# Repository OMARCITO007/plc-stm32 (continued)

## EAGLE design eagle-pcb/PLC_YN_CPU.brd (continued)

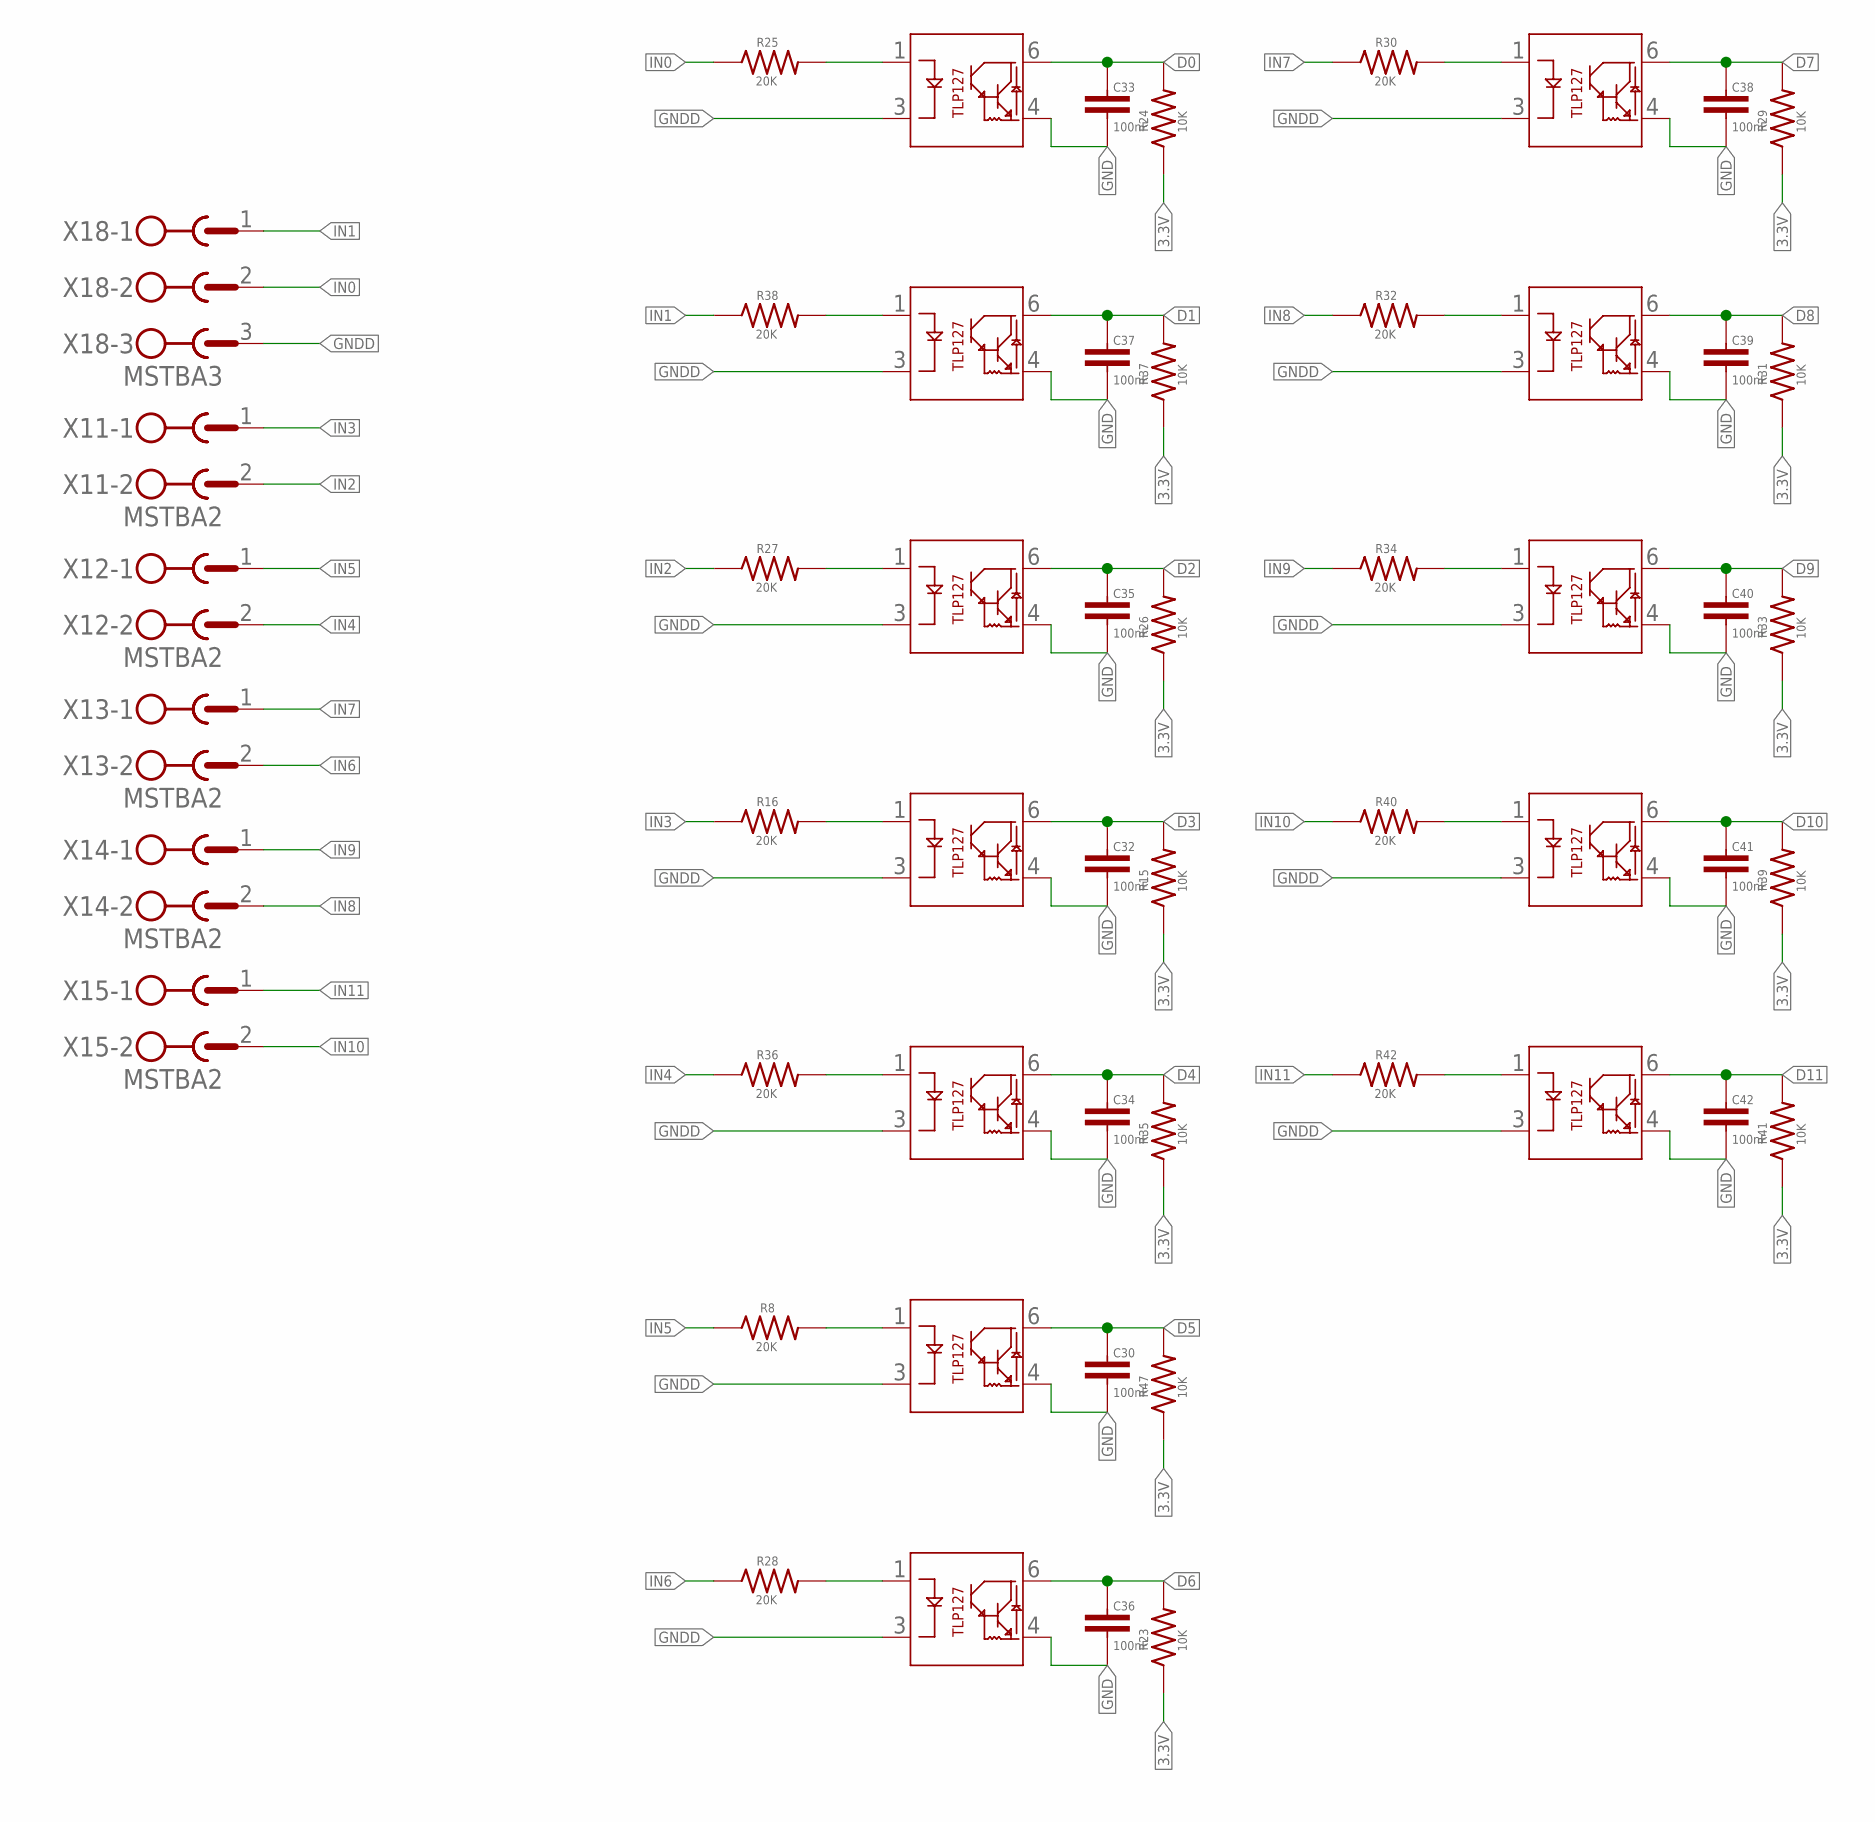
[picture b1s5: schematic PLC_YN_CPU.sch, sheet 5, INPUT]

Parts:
C30, C32, C33, C34, C35, C36, C37, C38, C39, C40, C41, C42: 100nF; C0603
R8, R16, R25, R27, R28, R30, R32, R34, R36, R38, R40, R42: 20K; SMD_1206
R15, R23, R24, R26, R29, R31, R33, R35, R37, R39, R41, R47: 10K; R0603
U8, U10, U12, U13, U14, U15, U16, U17, U18, U19, U20, U23: LTV-357T-B-IN; TLP127
X11, X12, X13, X14, X15: MSTBA2
X18: MSTBA3

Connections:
3.3V: R15.1, R23.1, R24.1, R26.1, R29.1, R31.1, R33.1, R35.1, R37.1, R39.1, R41.1, R47.1; also elsewhere on the board
D0: C33.1, R24.2, U18.6; also elsewhere on the board
D1: C37.1, R37.2, U23.6; also elsewhere on the board
D2: C35.1, R26.2, U20.6; also elsewhere on the board
D3: C32.1, R15.2, U14.6; also elsewhere on the board
D4: C34.1, R35.2, U16.6; also elsewhere on the board
D5: C30.1, R47.2, U8.6; also elsewhere on the board
D6: C36.1, R23.2, U13.6; also elsewhere on the board
D7: C38.1, R29.2, U10.6; also elsewhere on the board
D8: C39.1, R31.2, U12.6; also elsewhere on the board
D9: C40.1, R33.2, U15.6; also elsewhere on the board
D10: C41.1, R39.2, U17.6; also elsewhere on the board
D11: C42.1, R41.2, U19.6; also elsewhere on the board
GND: C30.2, C32.2, C33.2, C34.2, C35.2, C36.2, C37.2, C38.2, C39.2, C40.2, C41.2, C42.2, U8.4, U10.4, U12.4, U13.4, U14.4, U15.4, U16.4, U17.4, U18.4, U19.4, U20.4, U23.4; also elsewhere on the board
GNDD: U8.3, U10.3, U12.3, U13.3, U14.3, U15.3, U16.3, U17.3, U18.3, U19.3, U20.3, U23.3, X18.3
IN0: R25.1, X18.2
IN1: R38.1, X18.1
IN2: R27.1, X11.2
IN3: R16.1, X11.1
IN4: R36.1, X12.2
IN5: R8.1, X12.1
IN6: R28.1, X13.2
IN7: R30.1, X13.1
IN8: R32.1, X14.2
IN9: R34.1, X14.1
IN10: R40.1, X15.2
IN11: R42.1, X15.1
unnamed: R30.2, U10.1
unnamed: R16.2, U14.1
unnamed: R32.2, U12.1
unnamed: R34.2, U15.1
unnamed: R25.2, U18.1
unnamed: R40.2, U17.1
unnamed: R27.2, U20.1
unnamed: R42.2, U19.1
unnamed: R8.2, U8.1
unnamed: R28.2, U13.1
unnamed: R38.2, U23.1
unnamed: R36.2, U16.1

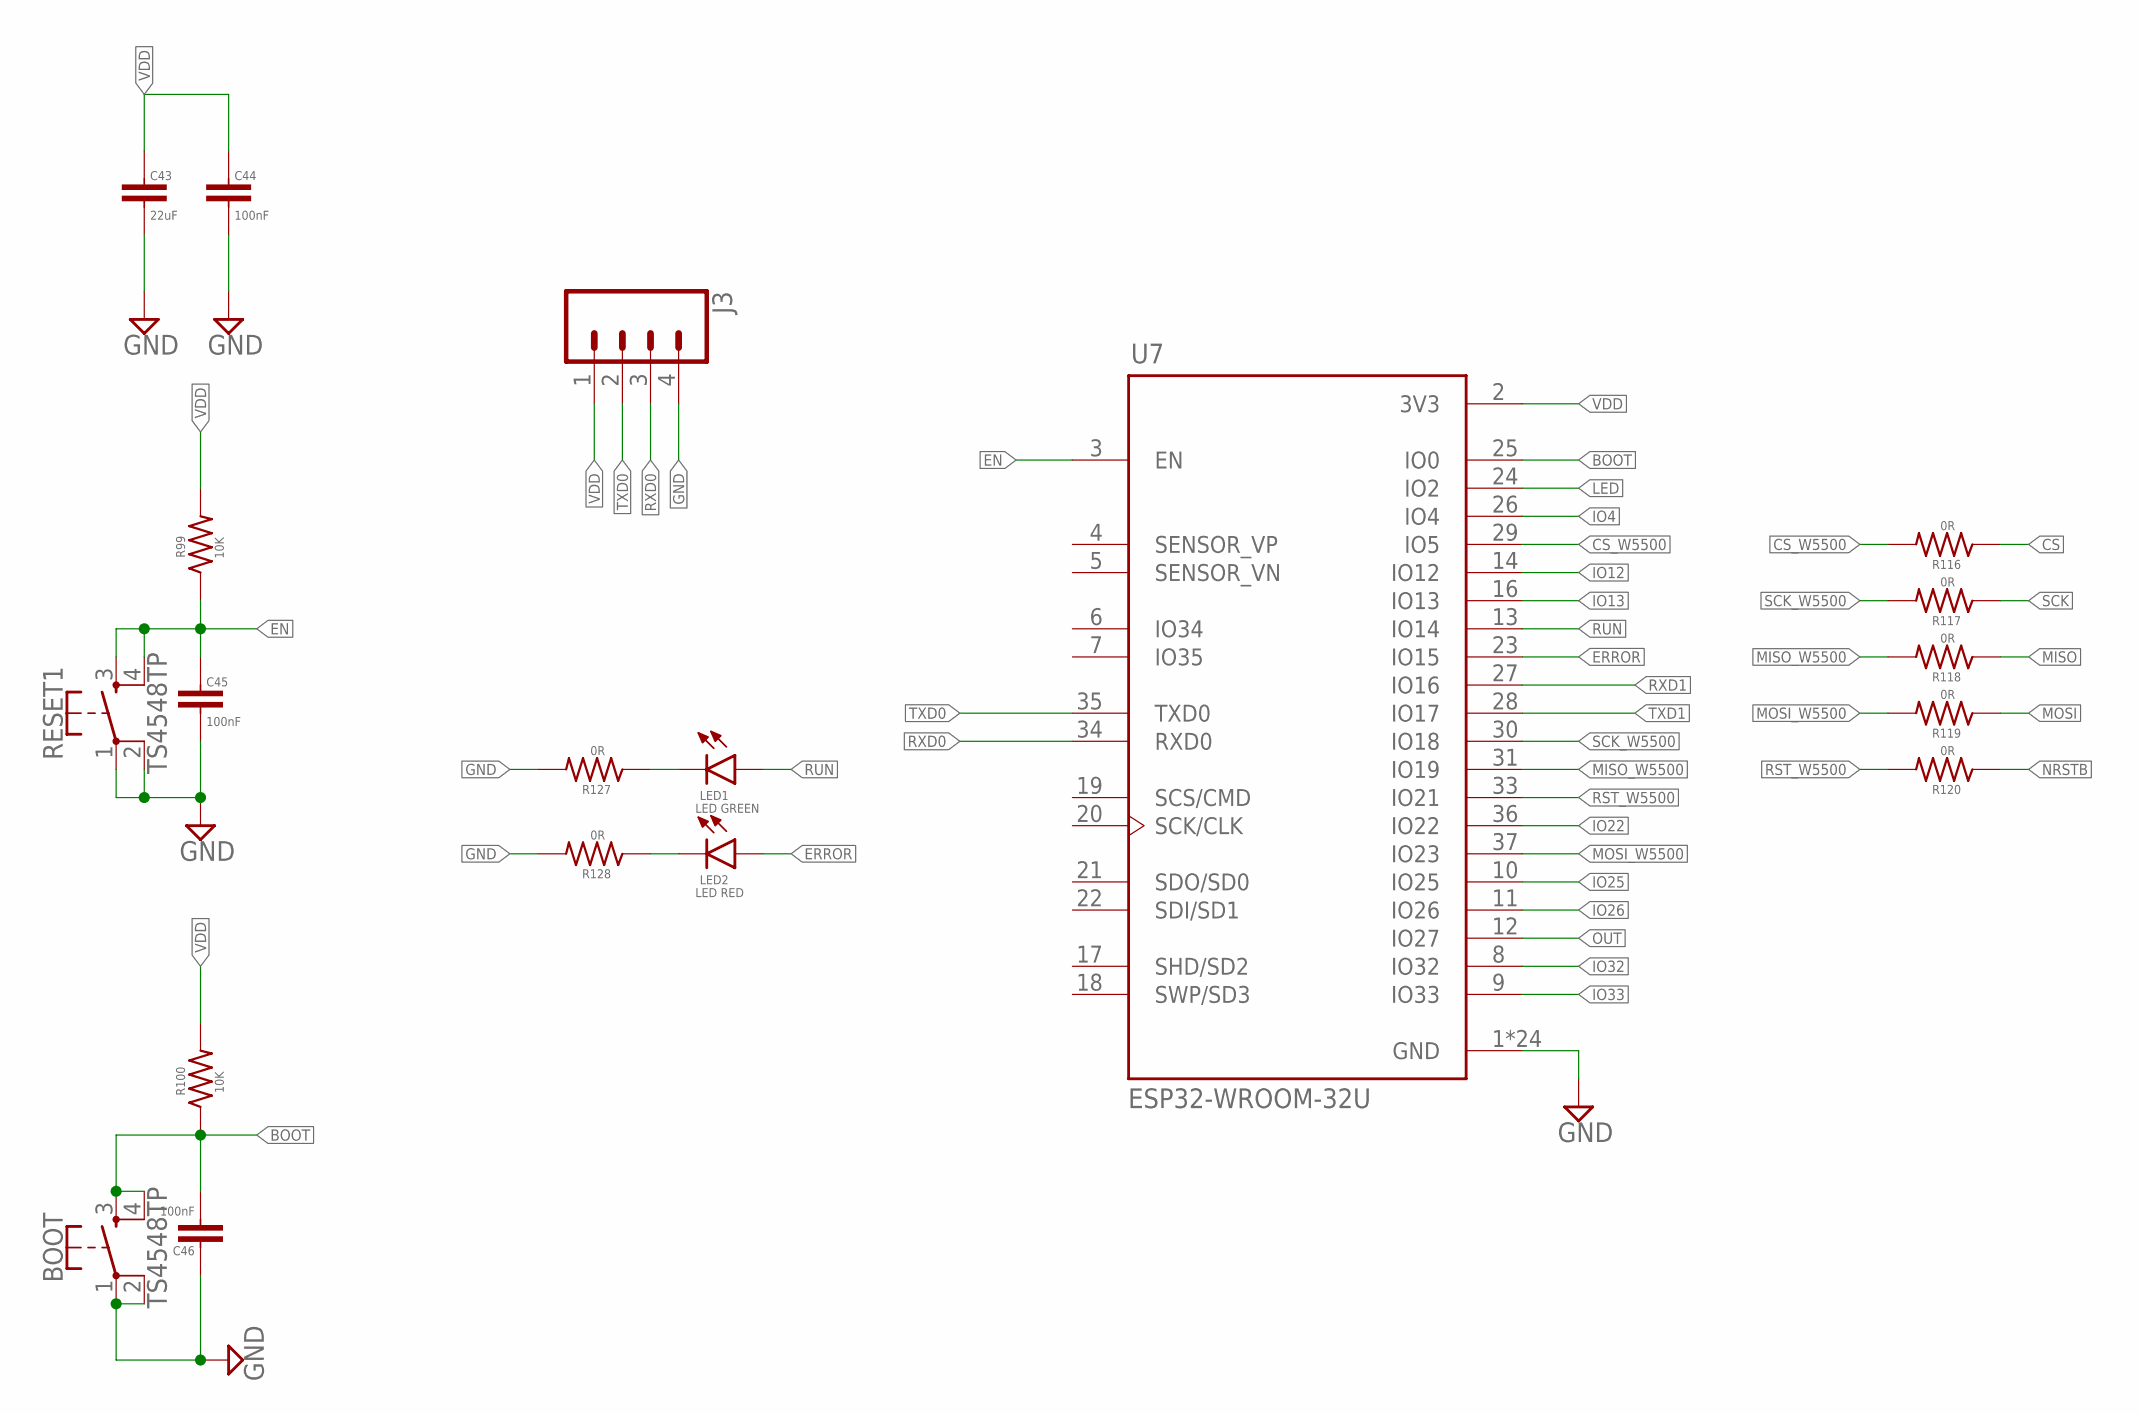
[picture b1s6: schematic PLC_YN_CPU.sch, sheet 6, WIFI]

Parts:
BOOT: TS4548TP; SWITCH
C43: 22uF; C0603
C44, C45, C46: 100nF; C0603
J3: CONN_04; 1X04
LED1: LED GREEN; L1206
LED2: LED RED; L1206
R99, R100: 10K; R0603
R116, R117, R118, R119, R120, R127, R128: 0R; R0603
RESET1: TS4548TP; SWITCH
U7: ESP32-WROOM-32U; MODULE_ESP32-WROOM-32D

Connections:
BOOT: BOOT.3, BOOT.4, C46.2, R100.1, U7.25 (IO0)
CS: R116.1; also elsewhere on the board
CS_W5500: R116.2, U7.29 (IO5)
EN: C45.1, R99.1, RESET1.3, RESET1.4, U7.3 (EN)
ERROR: LED2.A, U7.23 (IO15)
GND: BOOT.1, BOOT.2, C43.2, C44.2, C45.2, C46.1, J3.4, R127.2, R128.2, RESET1.1, RESET1.2, U7.1 (GND), U7.15 (GND), U7.38 (GND), U7.39_1 (GND), U7.39_2 (GND), U7.39_3 (GND), U7.39_4 (GND), U7.39_5 (GND), U7.39_6 (GND), U7.39_7 (GND), U7.39_8 (GND), U7.39_9 (GND), U7.39_10 (GND), U7.39_11 (GND), U7.39_12 (GND), U7.39_13 (GND), U7.39_14 (GND), U7.39_15 (GND), U7.39_16 (GND), U7.39_17 (GND), U7.39_18 (GND), U7.39_19 (GND), U7.39_20 (GND), U7.39_21 (GND); also elsewhere on the board
IO4: U7.26 (IO4)
IO12: U7.14 (IO12)
IO13: U7.16 (IO13)
IO22: U7.36 (IO22)
IO25: U7.10 (IO25)
IO26: U7.11 (IO26)
IO32: U7.8 (IO32)
IO33: U7.9 (IO33)
LED: U7.24 (IO2)
MISO: R118.1; also elsewhere on the board
MISO_W5500: R118.2, U7.31 (IO19)
MOSI: R119.1; also elsewhere on the board
MOSI_W5500: R119.2, U7.37 (IO23)
unnamed: LED1.C, R127.1
unnamed: LED2.C, R128.1
NRSTB: R120.1; also elsewhere on the board
OUT: U7.12 (IO27)
RST_W5500: R120.2, U7.33 (IO21)
RUN: LED1.A, U7.13 (IO14)
RXD0: J3.3, U7.34 (RXD0); also elsewhere on the board
RXD1: U7.27 (IO16)
SCK: R117.1; also elsewhere on the board
SCK_W5500: R117.2, U7.30 (IO18)
TXD0: J3.2, U7.35 (TXD0); also elsewhere on the board
TXD1: U7.28 (IO17)
VDD: C43.1, C44.1, J3.1, R99.2, R100.2, U7.2 (3V3); also elsewhere on the board

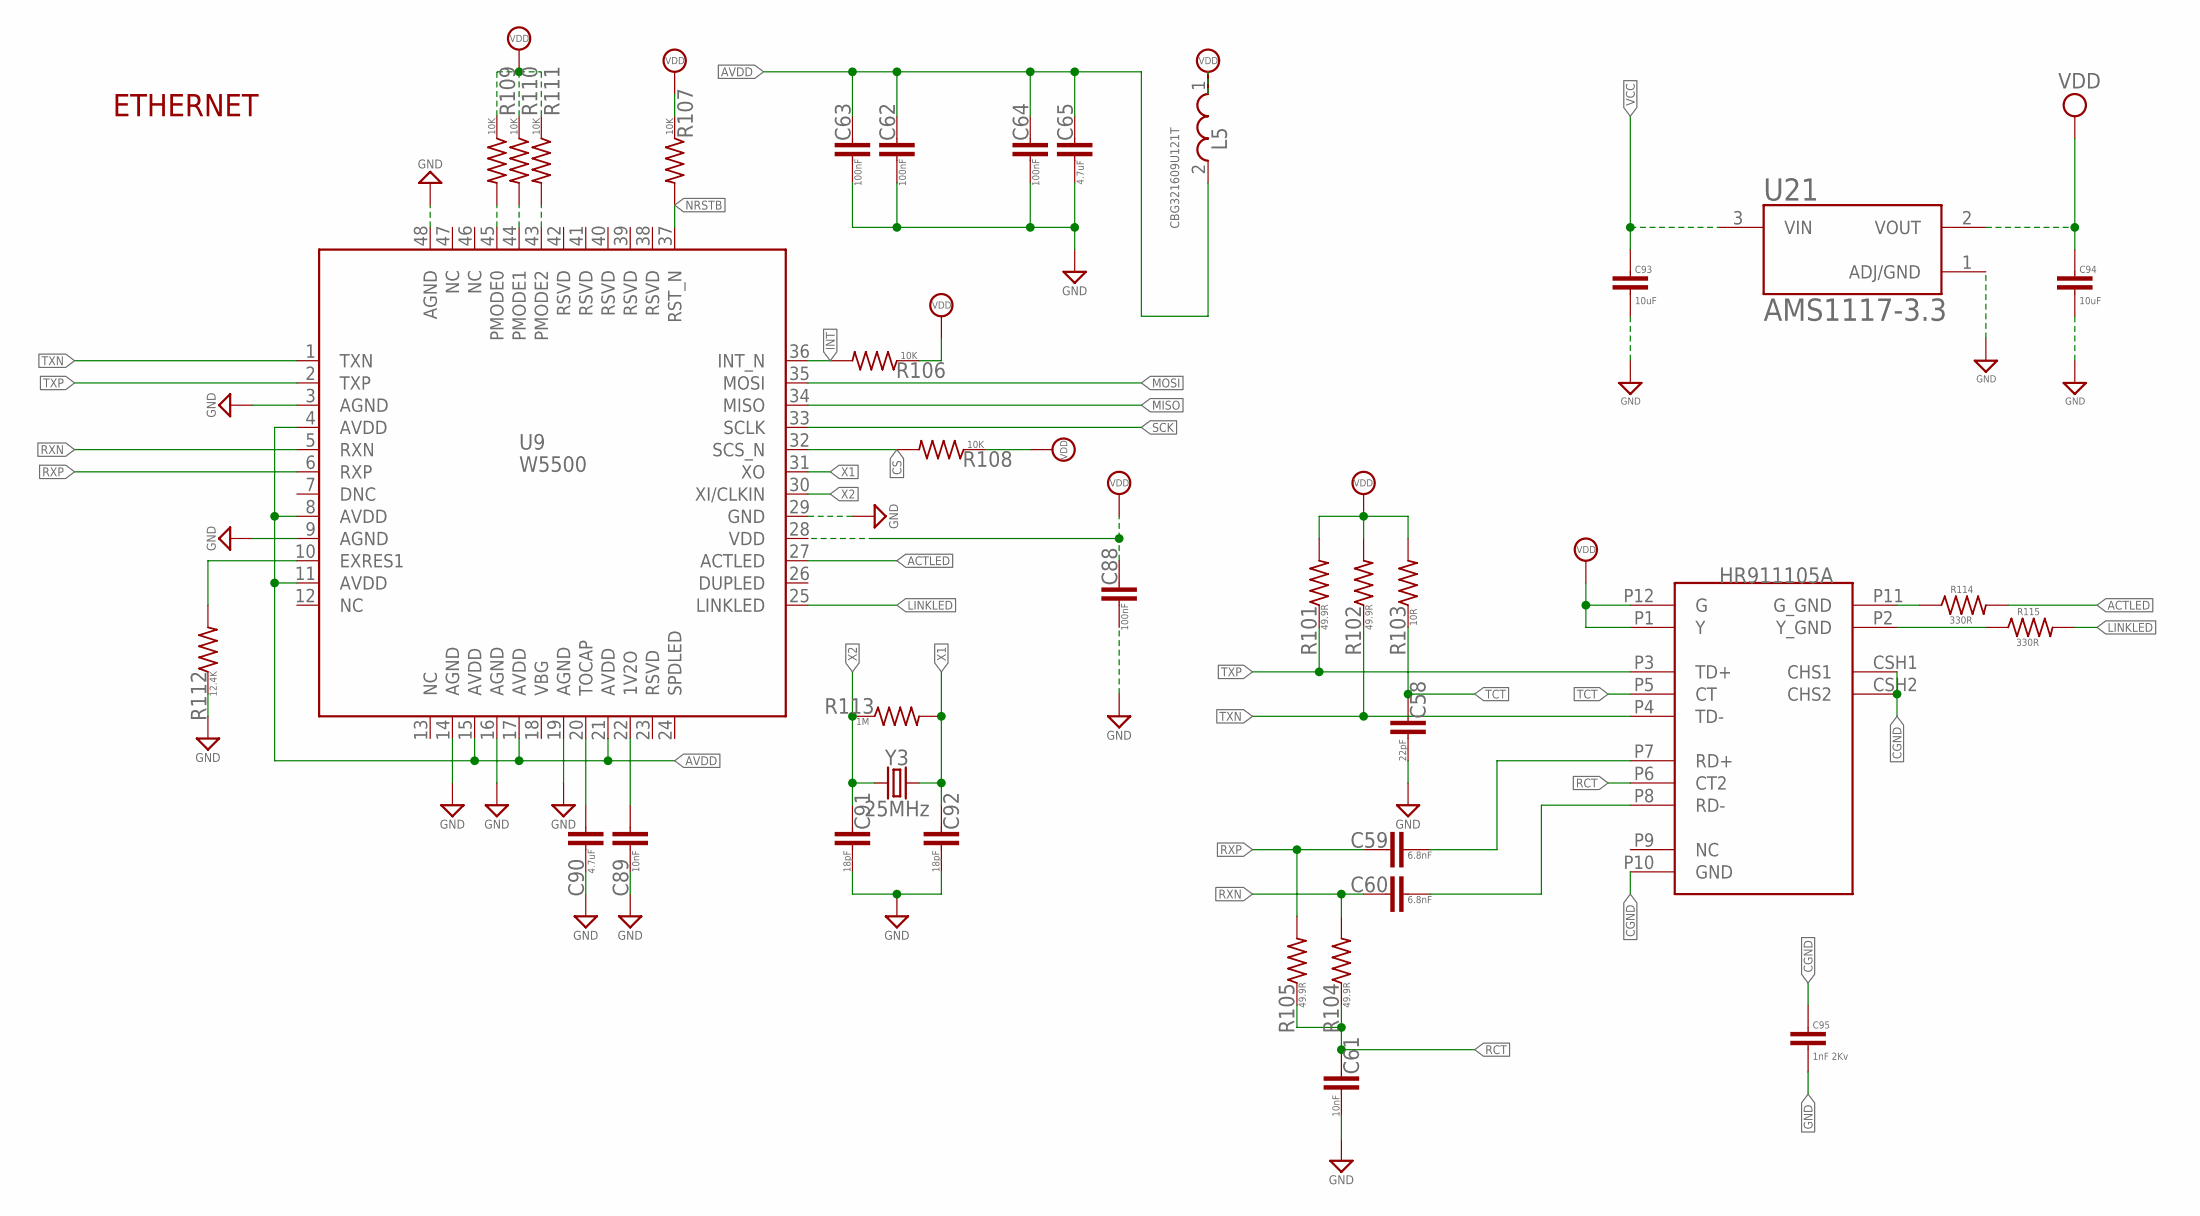
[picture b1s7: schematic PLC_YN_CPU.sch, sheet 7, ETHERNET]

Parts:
C58: 22pF; C0603
C59, C60: 6.8nF; C0603
C61, C89: 10nF; C0603
C62, C63, C64, C88: 100nF; C0603
C65, C90: 4.7uF; C0603
C91, C92: 18pF; C0603
C93, C94: 10uF; SMD_1206
C95: 1nF 2Kv; SMD_1206
L5: CBG321609U121T; SMD_1206
R101, R102, R104, R105: 49.9R; R0603
R103: 10R; R0603
R106, R107, R108, R109, R110, R111: 10K; R0603
R112: 12.4K; R0603
R113: 1M; R0603
R114, R115: 330R; R0603
U9: W5500
U21: AMS1117-3.3; SOT229P700X180-4N
X4: HR961160C
Y3: 25MHz; HC49UP

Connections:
ACTLED: R114.2, U9.27 (ACTLED)
AVDD: C62.1, C63.1, C64.1, C65.1, L5.2, U9.4 (AVDD), U9.8 (AVDD), U9.11 (AVDD), U9.15 (AVDD), U9.17 (AVDD), U9.21 (AVDD)
CGND: C95.1, X4.CSH1 (CHS1), X4.CSH2 (CHS2), X4.P10 (GND)
CS: R108.2, U9.32 (SCS_N); also elsewhere on the board
GND: C58.2, C61.2, C62.2, C63.2, C64.2, C65.2, C88.2, C89.2, C90.2, C91.2, C92.2, C93.2, C94.2, C95.2, R112.1, U9.3 (AGND), U9.9 (AGND), U9.14 (AGND), U9.16 (AGND), U9.19 (AGND), U9.29 (GND), U9.48 (AGND), U21.1 (ADJ/GND); also elsewhere on the board
INT: R106.2, U9.36 (INT_N)
LINKLED: R115.2, U9.25 (LINKLED)
MISO: U9.34 (MISO); also elsewhere on the board
MOSI: U9.35 (MOSI); also elsewhere on the board
unnamed: C59.2, X4.P7 (RD+)
unnamed: C60.2, X4.P8 (RD-)
unnamed: R111.2, U9.43 (PMODE2)
unnamed: C89.1, U9.22 (1V2O)
unnamed: C90.1, U9.20 (TOCAP)
unnamed: R112.2, U9.10 (EXRES1)
unnamed: R109.2, U9.45 (PMODE0)
unnamed: R110.2, U9.44 (PMODE1)
unnamed: R114.1, X4.P11 (G_GND)
unnamed: R115.1, X4.P2 (Y_GND)
NRSTB: R107.2, U9.37 (RST_N); also elsewhere on the board
RCT: C61.1, R104.1, R105.1, X4.P6 (CT2)
RXN: C60.1, R104.2, U9.5 (RXN)
RXP: C59.1, R105.2, U9.6 (RXP)
SCK: U9.33 (SCLK); also elsewhere on the board
TCT: C58.1, R103.1, X4.P5 (CT)
TXN: R102.1, U9.1 (TXN), X4.P4 (TD-)
TXP: R101.1, U9.2 (TXP), X4.P3 (TD+)
VCC: C93.1, U21.3 (VIN); also elsewhere on the board
VDD: C88.1, C94.1, L5.1, R101.2, R102.2, R103.2, R106.1, R107.1, R108.1, R109.1, R110.1, R111.1, U9.28 (VDD), U21.2 (VOUT), X4.P1 (Y), X4.P12 (G); also elsewhere on the board
X1: C92.1, R113.2, U9.31 (XO), Y3.2
X2: C91.1, R113.1, U9.30 (XI/CLKIN), Y3.1

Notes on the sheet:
ETHERNET

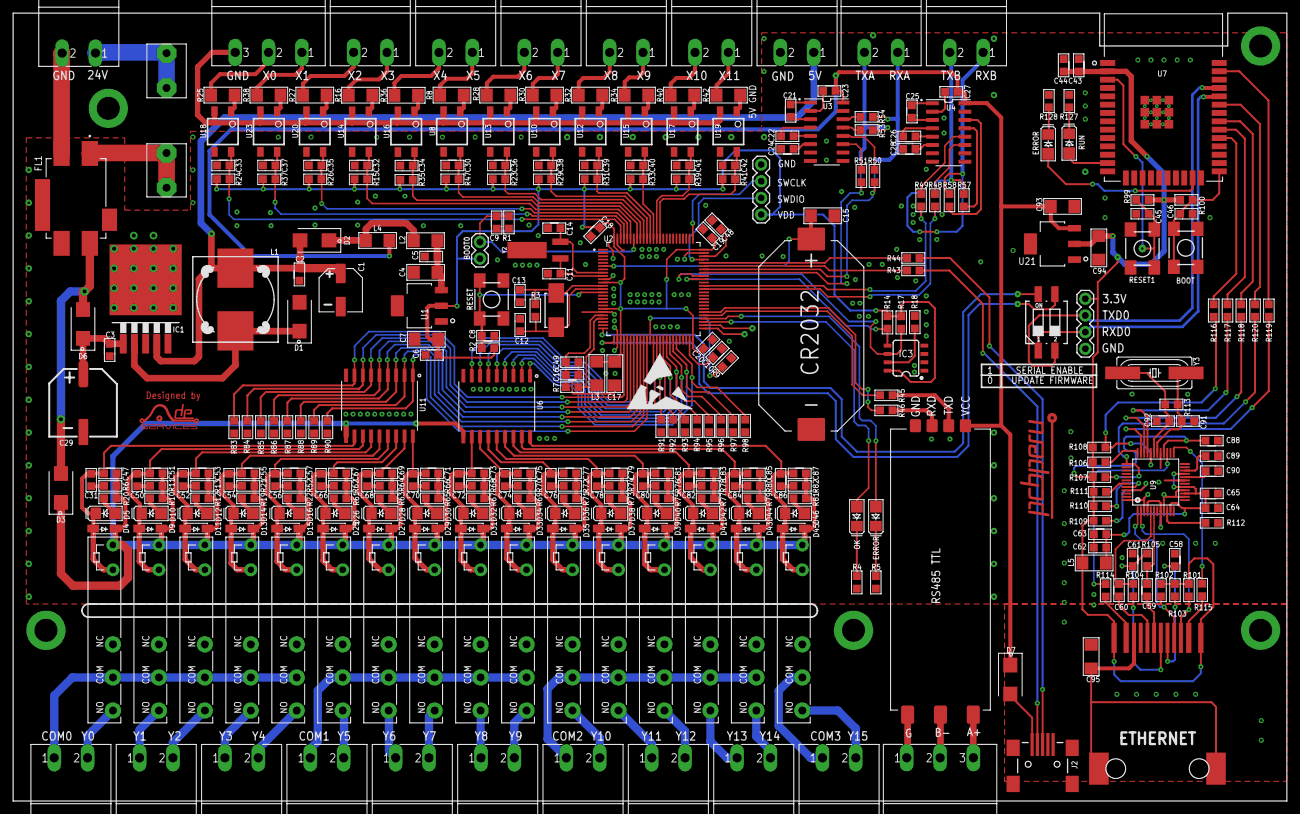
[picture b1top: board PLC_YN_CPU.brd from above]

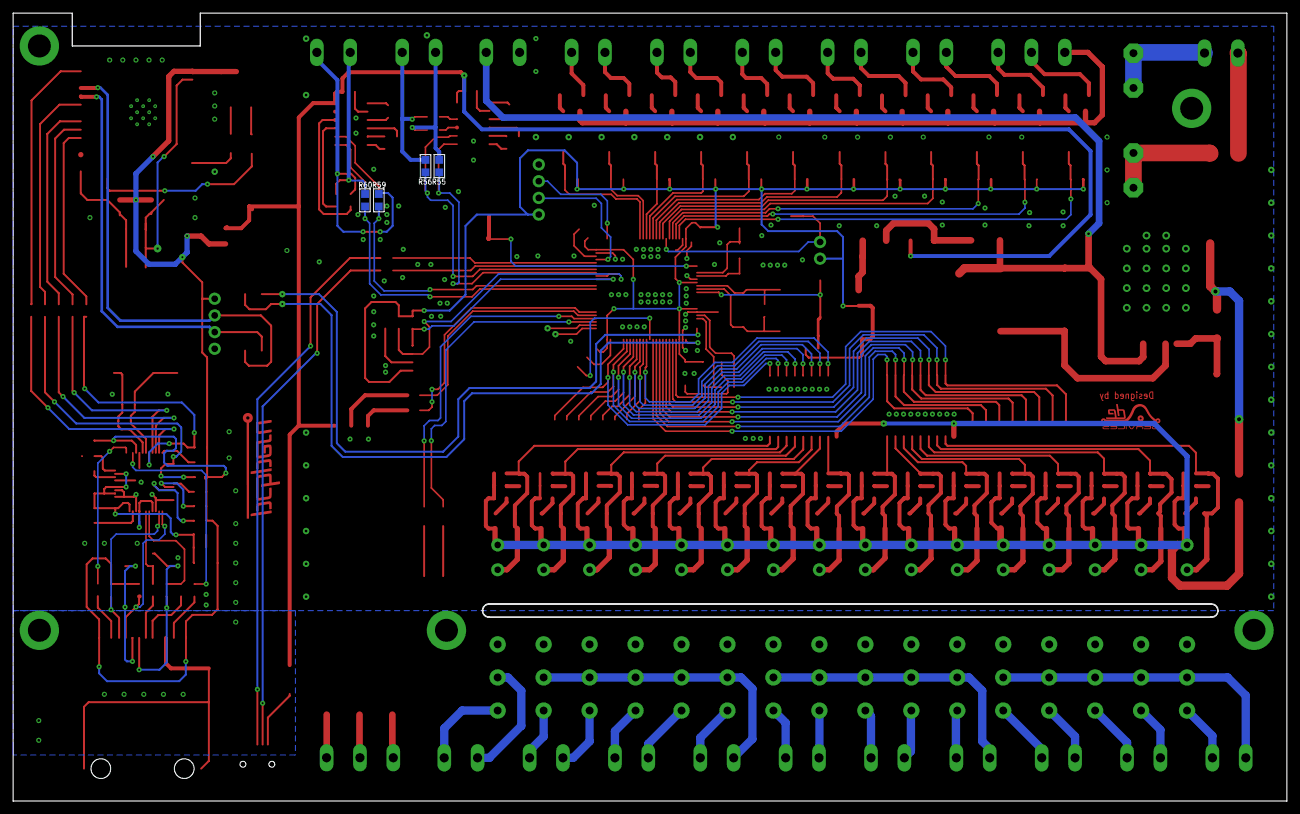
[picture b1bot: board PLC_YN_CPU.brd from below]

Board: 2 copper layers, 194.0 x 120.0 mm, 342 parts (4 on the bottom side), 239 nets.

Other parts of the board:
ES: ESD_10.00
U$2: PCB_PERU
U$3: ADE2021
